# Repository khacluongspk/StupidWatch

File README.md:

# Smart Watch project
Funny project

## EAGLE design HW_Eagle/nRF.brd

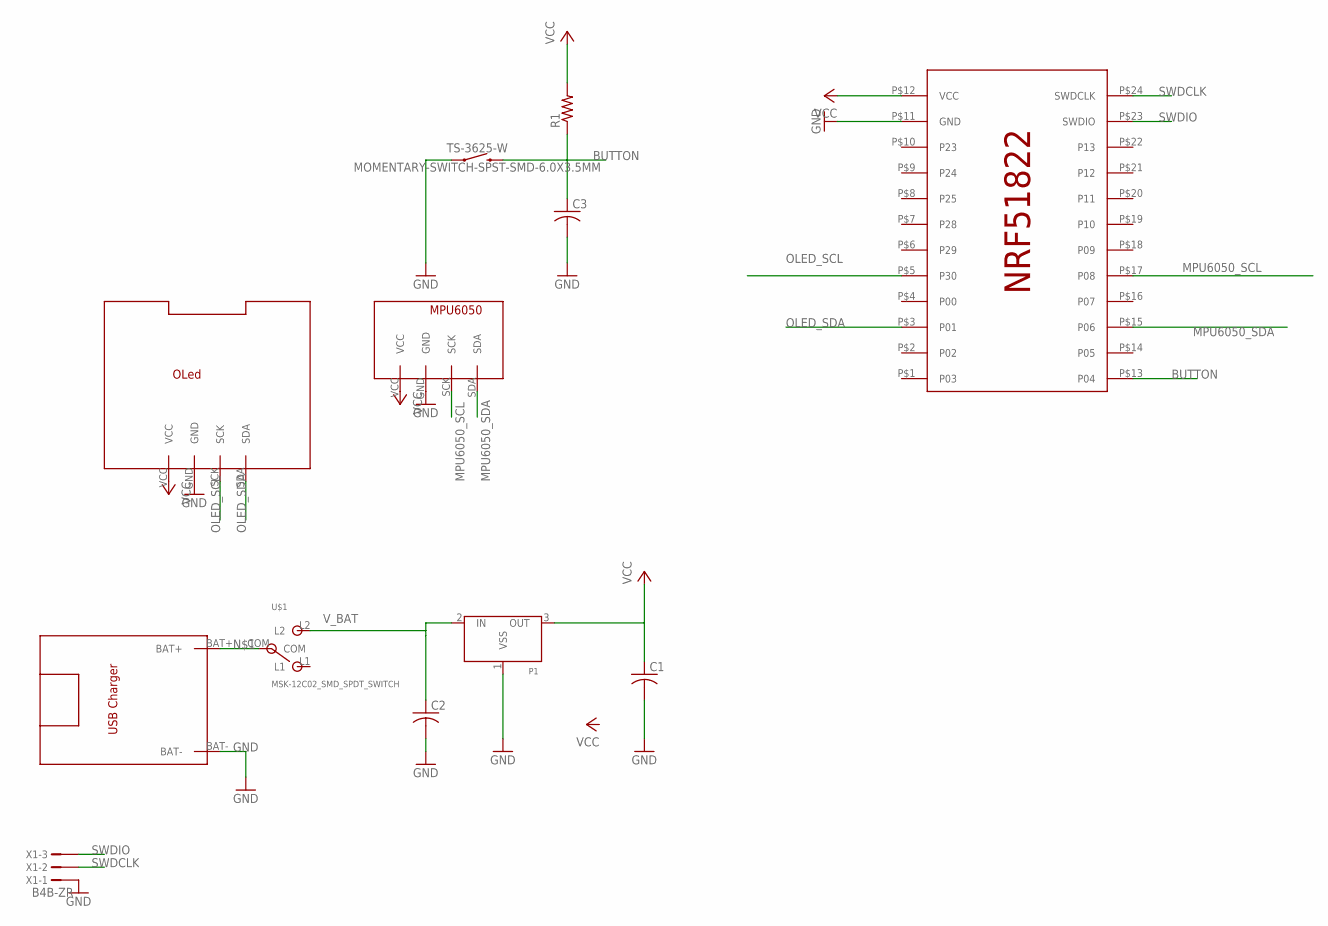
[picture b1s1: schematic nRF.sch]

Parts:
C1, C2: C-USC0805; C0805
C3: C-USC0603; C0603
P1: XC6206SOT-89; SOT-89
R1: R-US_R0603; R0603
TS-3625-W: MOMENTARY-SWITCH-SPST-SMD-6.0X3.5MM; TACTILE_SWITCH_SMD_6.0X3.5MM
U$1: MSK-12C02_SMD_SPDT_SWITCH; MSK-12C02
U$3: OLED; OLED_1.3_I2C
U$4: MPU60XX; MPU6050
U$5: NRF51822; NRF51822_HSHOP
U$6: TP4056
X1: B4B-ZR

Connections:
BUTTON: C3.1, R1.1, TS-3625-W.2, U$5.P$13 (P04)
GND: C1.2, C2.2, C3.2, P1.1 (VSS), TS-3625-W.1, U$3.GND, U$4.GND, U$5.P$11 (GND), U$6.BAT-, X1.1
MPU6050_SCL: U$4.SCK, U$5.P$17 (P08)
MPU6050_SDA: U$4.SDA, U$5.P$15 (P06)
unnamed: U$1.COM, U$6.BAT+
OLED_SCL: U$3.SCK, U$5.P$5 (P30)
OLED_SDA: U$3.SDA, U$5.P$3 (P01)
SWDCLK: U$5.P$24 (SWDCLK), X1.2
SWDIO: U$5.P$23 (SWDIO), X1.3
VCC: C1.1, P1.3 (OUT), R1.2, U$3.VCC, U$4.VCC, U$5.P$12 (VCC)
V_BAT: C2.1, P1.2 (IN), U$1.L2

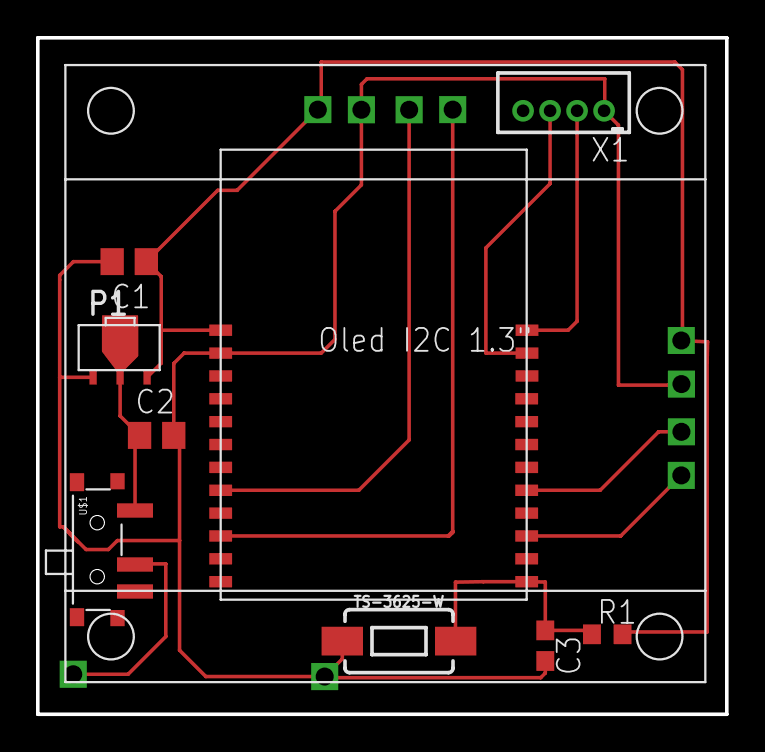
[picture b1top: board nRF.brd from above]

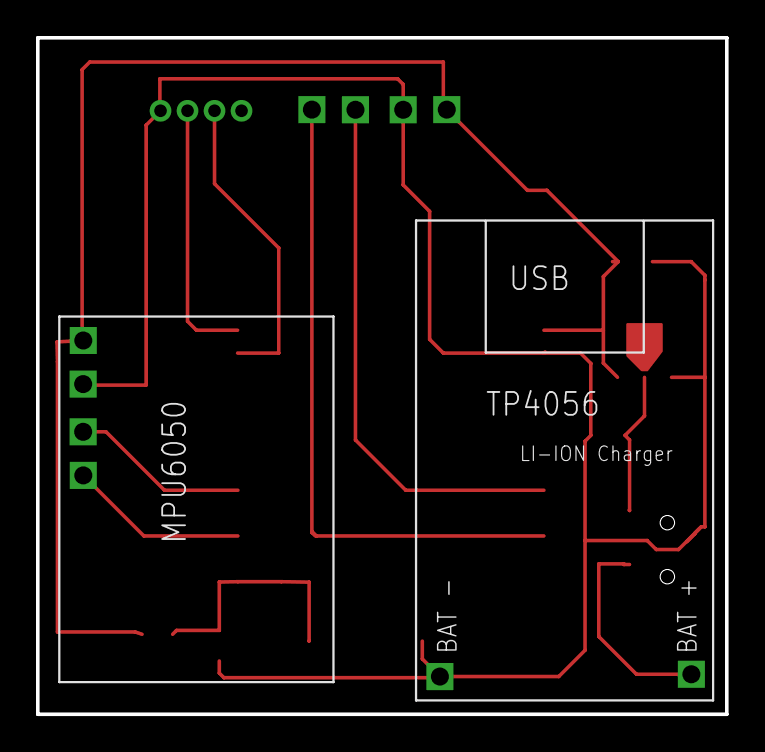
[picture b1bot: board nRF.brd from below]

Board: 2 copper layers, 38.3 x 37.6 mm, 12 parts (2 on the bottom side), 11 nets.

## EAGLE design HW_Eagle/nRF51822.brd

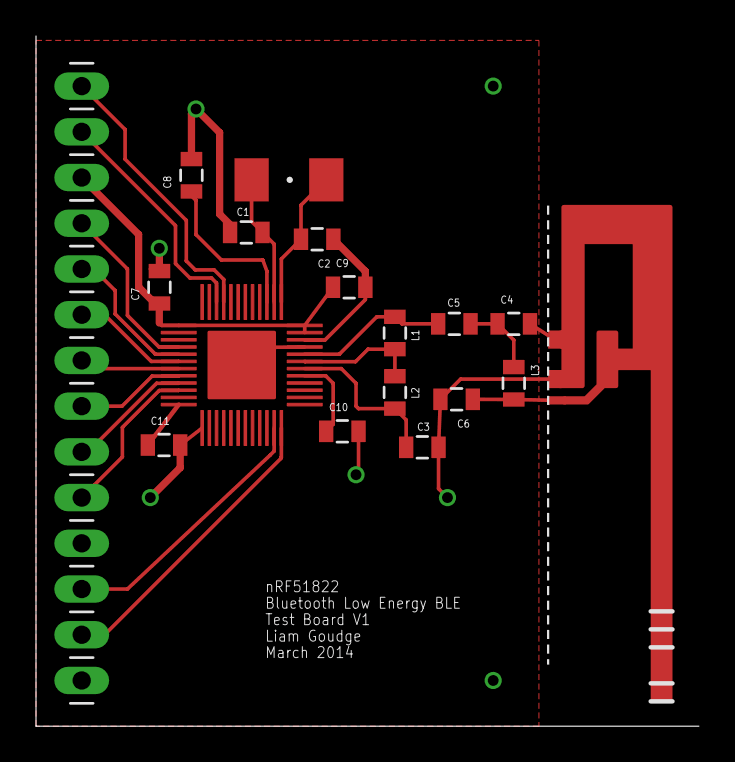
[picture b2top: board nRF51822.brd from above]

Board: 2 copper layers, 36.8 x 38.3 mm, 18 parts (0 on the bottom side), 21 nets.

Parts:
C1, C2: 12pF; 0805
C3: 2.2nF; 0805
C4: 1.0pF; 0805
C5: 2.2pF; 0805
C6: 1.5pF; 0805
C7, C8, C11: 100nF; 0805
C9: 1.0nF; 0805
C10: 47nF; 0805
L1: 4.7nH; 0805
L2: 10nH; 0805
L3: 3.3nH; 0805
Q1: FC-12M
U1: nRF51822; QFN48
U$2: INVERTED_F_ANTENNA+2; DN007+2
U$3: PINHD-1X14; 1X14

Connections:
unnamed: C1.2, Q1.1, U1.P38
unnamed: C2.2, Q1.2, U1.P37
unnamed: C3.1, L2.2, U1.P30
unnamed: U1.P45, U$3.1
unnamed: C8.1, U1.P39
unnamed: C5.1, L1.1, U1.P32
unnamed: C4.1, C5.2, L3.1
unnamed: C6.1, L3.2, U$2.FEED
unnamed: U1.P46, U$3.2
unnamed: U1.P4, U$3.4
unnamed: U1.P5, U$3.5
unnamed: L1.2, L2.1, U1.P31
unnamed: U1.P6, U$3.6
unnamed: U1.P7, U$3.7
unnamed: U1.P8, U$3.8
unnamed: U1.P9, U$3.9
unnamed: U1.P10, U$3.10
unnamed: U1.P23, U$3.12
unnamed: U1.P24, U$3.13
VDD: C7.1, C9.1, C10.1, C11.1, U1.P1, U1.P12, U1.P29, U1.P35, U1.P36, U$3.3
VSS: C1.1, C2.1, C3.2, C4.2, C6.2, C7.2, C8.2, C9.2, C10.2, C11.2, U1.P13, U1.P33, U1.P34, U1.VSS, U$2.GND, U$2.GND@1, U$3.11, U$3.14

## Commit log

2017-08-02 add mpu6050,ssd1306
2017-08-04 improve ssd1306.
2017-08-04 Imported from https://khacluongspk@github.com/khacluongspk/StupidWatch.git
2017-08-16 Add raw pedometer lib
2018-01-28 [HW] Add hardware files
2018-01-29 [HW] Add Batterry connector
2018-03-04 [HW] Change to using modules
2018-03-04 Add README.md
2018-03-15 Add regulator
2018-03-18 Change LDO package
2018-04-23 [HW] Add modules: Oled, MPU6050, TP4056
2018-05-01 [HW] Update HW v1.2

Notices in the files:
parts and their libraries:
SparkFun-Switches: Licensing: Creative Commons ShareAlike 4.0 International - https://creativecommons.org/licenses/by-sa/4.0
SparkFun-Capacitors: Licensing: CC v3.0 Share-Alike You are welcome to use this library for commercial purposes.
